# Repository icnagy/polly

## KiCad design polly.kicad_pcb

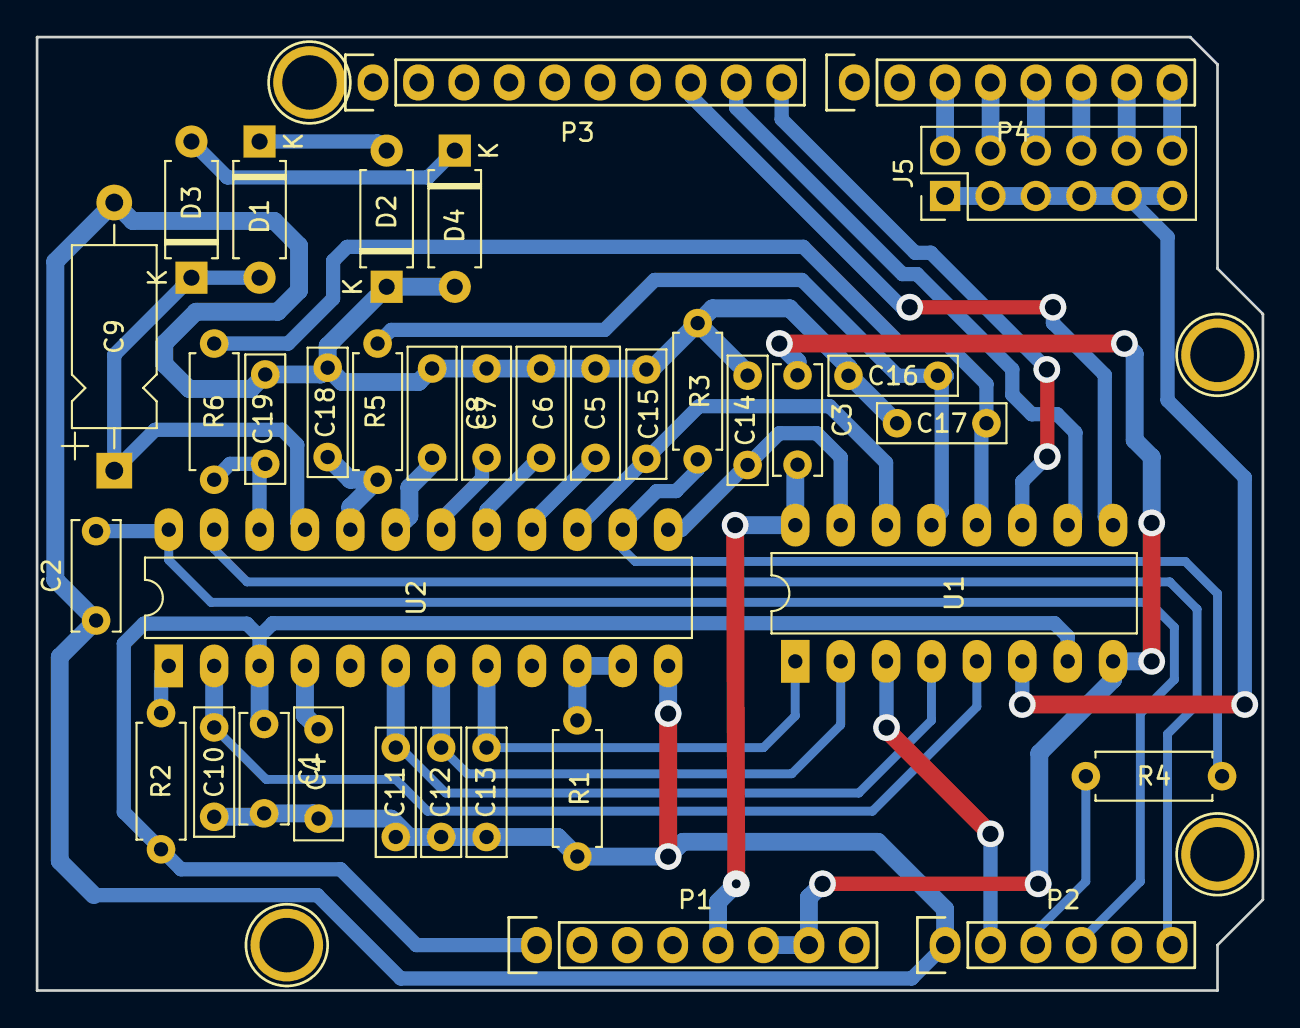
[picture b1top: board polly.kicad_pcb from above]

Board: 2 copper layers, 68.6 x 53.3 mm, 40 parts (0 on the bottom side), 39 nets.

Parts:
C1, C2, C3: 100nF; C_Disc_D6.0mm_W2.5mm_P5.00mm
C4: 2.2nF; C_Rect_L7.2mm_W2.5mm_P5.00mm_FKS2_FKP2_MKS2_MKP2
C5, C6, C7: 33nF; C_Rect_L7.2mm_W2.5mm_P5.00mm_FKS2_FKP2_MKS2_MKP2
C8: 560pF; C_Rect_L7.2mm_W2.5mm_P5.00mm_FKS2_FKP2_MKS2_MKP2
C9: 4.5uF; CP_Axial_L10.0mm_D4.5mm_P15.00mm_Horizontal
C10, C11, C12, C13, C14, C15, C16, C17: 10nF; C_Rect_L7.0mm_W2.0mm_P5.00mm
C18, C19: 1nF; C_Rect_L7.0mm_W2.0mm_P5.00mm
D1, D2, D3, D4: 1N4148; D_A-405_P7.62mm_Horizontal
J5: Conn_02x06_Odd_Even; PinHeader_2x06_P2.54mm_Vertical
P1: Power; Socket_Strip_Arduino_1x08
P2: Analog; Socket_Strip_Arduino_1x06
P3: Digital; Socket_Strip_Arduino_1x10
P4: Digital; Socket_Strip_Arduino_1x08
P5, P6, P7, P8: CONN_01X01; Arduino_1pin
R1, R3: 1k; R_Axial_DIN0207_L6.3mm_D2.5mm_P7.62mm_Horizontal
R2: 240k; R_Axial_DIN0207_L6.3mm_D2.5mm_P7.62mm_Horizontal
R4: 68k; R_Axial_DIN0207_L6.3mm_D2.5mm_P7.62mm_Horizontal
R5, R6: 1M; R_Axial_DIN0207_L6.3mm_D2.5mm_P7.62mm_Horizontal
U1: 4051; DIP-16_W7.62mm_LongPads
U2: AS3394E; DIP-24_W7.62mm_LongPads

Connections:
+5V: C3.2, P1.5, U1.16
+5VA: C2.2, P2.4, U2.24
/CUTOFF: C16.1, R5.2, U1.13
/DAC_OUTPUT: P2.2, U1.3
/LP_CUTOFF: C18.1, R5.1, U2.20
/LP_VCA_CV: C19.1, R6.1, U2.22
/MIXER_CV: C14.1, U1.15, U2.13
/MOD_AMT: C11.1, U1.4, U2.6
/NOISE: P2.3, R4.1
/PARAM_SEL_A: P3.8, U1.9
/PARAM_SEL_B: P3.9, U1.10
/PARAM_SEL_C: P3.10, U1.11
/PWM: C13.1, U1.1, U2.8
/RESONANCE: C15.1, U1.14, U2.15
/VCA_CV: C17.1, R6.2, U1.12
/VCO_CV: C10.1, U1.5, U2.2
/VOICE_OUT: P2.6, U2.23
/WAVE_SEL: C12.1, U1.2, U2.7
/~VOICE_1_SEL: J5.12, P4.8
/~VOICE_2_SEL: J5.10, P4.7
/~VOICE_3_SEL: J5.8, P4.6
/~VOICE_4_SEL: J5.6, P4.5
/~VOICE_5_SEL: J5.4, P4.4
/~VOICE_6_SEL: J5.2, P4.3
/~VOICE_SEL: J5.1, J5.3, J5.5, J5.7, J5.9, J5.11, U1.6
GND: C3.1, P1.6, P1.7, U1.8
GNDA: C1.2, C2.1, C4.2, C5.1, C6.1, C7.1, C8.1, C9.2, C10.2, C11.2, C12.2, C13.2, C14.2, C15.2, C16.2, C17.2, C18.2, C19.2, D2.1, D4.2, P2.1, R1.2, R3.2, U2.12
unnamed: C4.1, U2.4
unnamed: C5.2, U2.16
unnamed: C6.2, U2.17
unnamed: C7.2, U2.18
unnamed: C8.2, U2.19
unnamed: C9.1, D1.2, D3.1, U2.21
unnamed: D1.1, D2.2
unnamed: D3.2, D4.1
unnamed: R1.1, U2.10, U2.11
unnamed: R2.1, U2.1
unnamed: R3.1, R4.2, U2.14
VEE: C1.1, P1.1, R2.2, U1.7, U2.3

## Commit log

2021-08-22 Adjust layout
2021-08-29 Imporove layout for single sided, add previous versions
2021-12-16 Added smoothing RC to VCF/VCA [just guessing?]
